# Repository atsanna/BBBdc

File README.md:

# BeagleBone Black Door Cape
This is a BeagleBone Black Cape designed for electronically locking or
unlocking a single door.  It can control either a 12V door strike or
a 12V door magnet.

You can order this PCB from oshpark here: https://oshpark.com/shared_projects/fA7vdbq6

The cape has the following features:
* Dual relays to ensure door is closed if a relay fails
* opto-isolated GPIO inputs for detecting door status and/or relay failure
* Jumpers for configuring door strike or door magnet (NO/NC)
* on-board voltage regulator so BBB can be powered via 12V
* connectors for two external software controlled 12V lamps
* LED indicators for 12V, 5V, relay engagement, and external lamps
* 24C256 EEPROM w/ address configurable via jumpers
* headers for an RPi/Arduino-compatible realtime clock module

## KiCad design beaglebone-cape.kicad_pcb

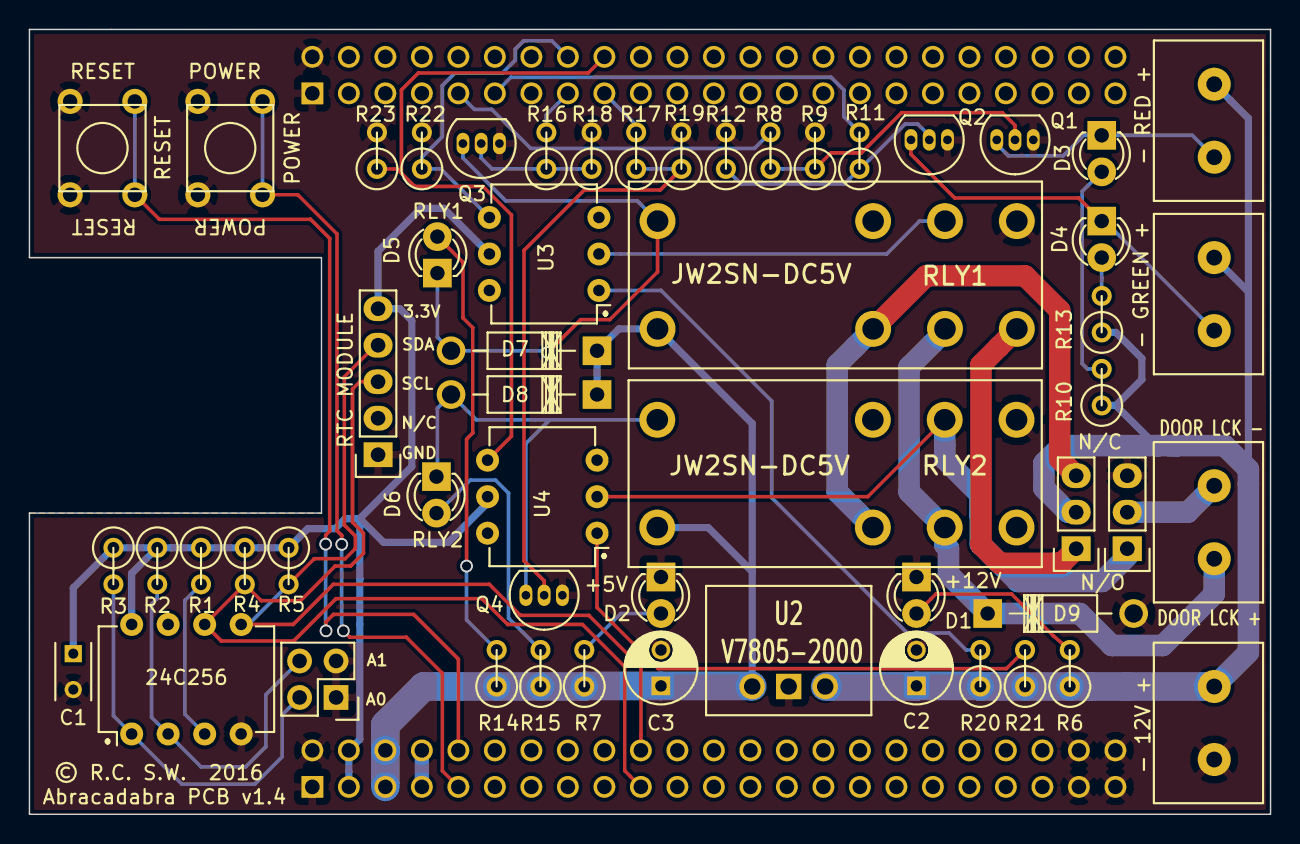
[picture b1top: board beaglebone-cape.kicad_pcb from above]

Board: 2 copper layers, 86.4 x 54.6 mm, 56 parts (0 on the bottom side), 40 nets.

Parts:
C1: 0.1uF (25V); C_Rect_L4_W2.5_P2.5
C2: 10 uF (25V); C_Radial_D5_L6_P2.5
C3: 22 uF (16V); C_Radial_D5_L6_P2.5
D1: PWR +12V; LED-3MM
D2: PWR +5V; LED-3MM
D3: RED; LED-3MM
D4: GREEN; LED-3MM
D5, D6: RELAY ON; LED-3MM
D7, D8, D9: 1N4007; Diode_DO-41_SOD81_Horizontal_RM10
P1: BEAGLEBONE_BLACK; BEAGLEBONE_BLACK_NO_PERIMETER
P2: 12V; TERM_BLOCK_ED2609
P3: RED_LIGHT; TERM_BLOCK_ED2609
P4: JUMPERS; Pin_Header_Straight_2x02
P5: GREEN_LIGHT; TERM_BLOCK_ED2609
P6: RTC MODULE; Pin_Header_Straight_1x05
P7, P8: NC/NO JUMPER; Pin_Header_Straight_1x03
P9: DOOR STRIKE/MAGNET; TERM_BLOCK_ED2609
Q1, Q2, Q3, Q4: 2N7000; TO-92_Inline_Narrow_Oval
R1, R2, R3: 4.7k; R1
R4, R5: 5.6k; R1
R6, R10, R13, R20, R21: 1k; R1
R7, R8, R11, R14, R15, R16, R17: 330; R1
R9, R12, R18, R19: 10k; R1
R22, R23: 2k; R1
RLY1, RLY2: JW2SN-DC5V; Panasonic_JW
SW1: PWR_SWITCH; BUTTON_MJTP1230
SW2: RESET_SWITCH; BUTTON_MJTP1230
U1: 24C256; DIP-8_W7.62mm
U2: V7805-2000; V78XX-2000
U3, U4: 4N25; DIP-6_W7.62mm

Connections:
+3V3: C1.1, P1.B3, P1.B4, P6.5, R1.1, R2.1, R3.1, R4.1, R5.1, U1.8, U3.5, U4.5
+5V: C3.1, D7.1, D8.1, P1.B5, P1.B6, R7.1, R14.1, R15.1, RLY1.1, RLY2.1, U2.VO
+12V: C2.1, P2.2, P3.2, P5.2, P8.2, R6.1, R10.1, R13.1, R20.1, R21.1, U2.VI
/A0: P4.2, R3.2, U1.1
/A1: P4.4, R2.2, U1.2
/A2: R1.2, U1.3
/GPIO_45: P1.A11, R11.2
/GPIO_69: P1.A9, R8.2
/I2C2_SCL: P1.B19, P6.3, R4.2, U1.6
/I2C2_SDA: P1.B20, P6.4, R5.2, U1.5
/LOCK_RELAYS/R1_ENGAGE: P1.A15, R16.2
/LOCK_RELAYS/R1_READ: P1.A16, R22.1, U3.4
/LOCK_RELAYS/R2_ENGAGE: P1.A17, R17.2
/LOCK_RELAYS/R2_READ: P1.A18, R23.1, U4.4
/PWR_BUT: P1.B9, SW1.1
/SYS_5V: P1.B7, P1.B8
/SYS_RESETn: P1.B10, SW2.1
GND: C1.2, C2.2, C3.2, D1.1, D2.1, D9.2, P1.A1, P1.A2, P1.B1, P1.B2, P1.B43, P1.B44, P1.B45, P1.B46, P2.1, P4.1, P4.3, P6.1, P7.3, Q1.1, Q2.1, Q3.1, Q4.1, R9.2, R12.2, R18.2, R19.2, R22.2, R23.2, RLY1.5, RLY2.5, SW1.2, SW2.2, U1.4, U2.GND
unnamed: D1.2, R6.2
unnamed: D2.2, R7.2
unnamed: D3.1, P3.1, Q1.3
unnamed: D3.2, R10.2
unnamed: D4.1, P5.1, Q2.3
unnamed: D4.2, R13.2
unnamed: D5.1, D7.2, Q3.3, RLY1.8
unnamed: D5.2, R14.2
unnamed: D6.1, D8.2, Q4.3, RLY2.8
unnamed: D6.2, R15.2
unnamed: D9.1, P9.1, RLY1.3, RLY2.3
unnamed: P7.1, RLY2.6, U4.2
unnamed: P7.2, P9.2
unnamed: P8.1, RLY1.4
unnamed: P8.3, RLY1.2, RLY2.2
unnamed: Q1.2, R8.1, R9.1
unnamed: Q2.2, R11.1, R12.1
unnamed: Q3.2, R16.1, R18.1
unnamed: Q4.2, R17.1, R19.1
unnamed: R20.2, U3.1
unnamed: R21.2, U4.1
unnamed: RLY1.6, U3.2

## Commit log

2015-11-08 Created power schematic
2015-11-08 Got everything done except lock relays
2015-11-08 Clean up schematic
2015-11-12 Added relay library, got locks drawn to the point where I have no idea how to hook things up
2015-11-14 Lock relay page looks done, still needs circuit check
2015-11-14 Converted jumpers to DPDT switch
2015-11-14 Started trimming down to a single relay
2015-11-14 Drew with a single relay & switch (both DPDT)
2015-11-14 Clean up library paths
2015-11-14 Cleaned up libraries
2015-11-18 Fixed BBB header labels, added some more lights and feed some gpio pins to detect lock status.
2015-11-18 updated the readme
2015-11-18 Added relay data sheet
2015-11-18 Added a netlist and started fixing rule check errors
2015-11-25 changed version
2015-11-26 schematic version 2.0 - redrawn w/ dpdt relays
2015-11-26 Addded RTC to readme
2015-11-28 Added opto-isolators, get ERC to pass, fix DPDT relay pictures
2015-11-28 Added relay datasheet to schematic
2015-11-29 Working towards v2.2
2015-11-29 Finished schematic changes for v2.2
2015-11-29 Added footprints for relays and switching regulator
2015-12-01 Added v2.2 schematic and the module libraries to the fp-lib-table
2015-12-04 built a net list, probably wrong parts but it's a start
2015-12-04 not sure what I just did
2015-12-07 Imported parts to pcbnew but its a mess
2015-12-07 Ironed out footprints with Rob, started placing stuff
2015-12-07 Moved a bunch of footprints around
2015-12-07 unbelievably managed to squeeze everything on the board
2015-12-07 tweaking of component placement on board
2015-12-07 Added new version of beaglebone module
2015-12-15 Finished 90% of traces and no ground planes yet
2015-12-15 lines all connected, need to connect ground pins
2015-12-15 only 2 GND nets to connect. Not sure what's wrong w/ them
2015-12-19 Added custom footprints & data sheets
2015-12-19 Placed new footprints, re-arrange things to make power layout better.
2015-12-20 Working on power tracks
2015-12-20 Finished first crack at laying power
2015-12-20 Added date and versioning to pcb
2015-12-22 Changed all power track widths to 2mm, made slight path change to 5V net
2015-12-28 layin pipe
2015-12-28 Still working on tracks
2015-12-28 Got DRC check to pass on pcb
2015-12-28 Cleaned up silk screening, adjust module alignment
2015-12-29 Updated documentation, tag as v1.11
2015-12-30 Tweaking traces
2015-12-30 pcb - about to change jumpers. Most other fixes are done
2015-12-30 Finished moving jumpers together on pcb
2015-12-30 Finished polishing up latest changes while sitting in the coffee exchange
2015-12-30 Finalized pcb v1.2
2016-01-03 Moved panasonic and relay modules into pretty local library. Added 3d files for button
2016-01-03 replaced the 3d models for buttons
2016-01-03 Added 3d model for Panasonic relays, update changelog, change version#
2016-01-03 Change silkscreen labels for power & relay LEDs
2016-01-09 flipped q3 around 180 deg.
2016-01-09 Changed track widths from 2.0 to 1.5
2016-01-09 Bumped up track width for 3.3V rail
2016-01-09 Added TODO list, almost there
2016-01-09 Added silkscreen comments, copyright
2016-01-10 Flipped RTC module, rearranged resistors R1-R5, add A0 A1 to silk screen for jumpers
2016-01-10 fixed EEPROM addressing in schmeatic, working on routing pcb now
2016-01-11 Finished pcb v1.3 and schematic v2.3
2016-01-11 tweaking silk screen, checked dimensions
2016-01-13 tweaking silk screen, checked dimensions, ready for mfg
2016-01-27 Added TODO
2016-01-27 Added a couple more things TODO
2016-07-29 fix years in changelog
2016-08-04 renamed hocuspocus library to abracadabra, fixed mask on panasonic relay library module, added R23, fixed wiring for relays
2016-08-04 fixed solder mask on bottom relays
2016-08-05 fixed relay and terminal block
2016-08-07 Almost fixed all pcb footprints so exchanging footprints w/ the schematic doesn't screw things up.
2016-08-07 Finished fixing footprints, added dots to chips, added more version info to silkscreen, updated TODO. Only thing left is to move top row of resistors closer to RLY1.
2016-08-10 Moved top row of resistors away from headers to make it easier to solder, did some cleanup of silkscreen labelling.
2016-08-10 Updated documentation for pcb v1.4 and schema v2.4
2016-08-10 Added polarity to terminal blocks on front silkscreen, added picture for readme.
2016-08-10 Forgot to save door lock silk screen changes
2016-08-11 Deleted old gerbers
2017-04-02 added osh park link

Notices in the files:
beaglebone-cape.kicad_pcb:
License: GPL v3, https://github.com/bubbapizza/BBBdc
© R.C., S.W.  2016
